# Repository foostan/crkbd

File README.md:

# Corne keyboard

The Corne keyboard is a split keyboard with 3x6 column staggered keys
and 3 thumb keys, based on [Helix](https://github.com/MakotoKurauchi/helix).
Crkbd stands for Corne Keyboard.

## Latest versions
- corne-cherry: for Cherry MX compatible switches

  - v4 Hotswappable ([JP](docs/corne-cherry/v4/buildguide_jp.md)/[EN](docs/corne-cherry/v4/buildguide_en.md))
  - v4 Soldering (will be released)
- corne-chocolate: for Kailh choc v1 and v2 switches
  - v4 Hotswappable ([JP](docs/corne-chocolate/v4/buildguide_jp.md)/[EN](docs/corne-chocolate/v4/buildguide_en.md)):
  - v4 Soldering (will be released)

## Old versions

- corne-classic: for Cherry MX compatible switches 
  - v1 Soldering: ([JP](docs/corne-classic/buildguide_jp.md)/[EN](docs/corne-classic/buildguide_en.md))
- corne-cherry: for Cherry MX compatible switches
  - v2 Hotswappable: ([JP](docs/corne-cherry/v2/buildguide_jp.md)/[EN](docs/corne-cherry/v2/buildguide_en.md))
  - v2 Hotswappable tilting version: ([tilting, JP](docs/corne-cherry/v2/buildguide_tilting_tenting_plate_jp.md)/[tilting, EN](docs/corne-cherry/v2/buildguide_tilting_tenting_plate_en.md)):
  - v3 Hotswappable: ([JP](docs/corne-cherry/v3/buildguide_jp.md)/[EN](docs/corne-cherry/v3/buildguide_en.md))
- corne-chocolate: for Kailh choc v1 switches
  - v2 Hotswappable: ([JP](docs/corne-chocolate/v2/buildguide_jp.md)/[EN](docs/corne-chocolate/v2/buildguide_en.md)):
- corne-light: for easy build with a simple PCB
  - v1 Soldering: ([JP](docs/corne-light/v1/buildguide_jp.md)/[EN](docs/corne-light/v1/buildguide_en.md)):
  - v2 Soldering: ([JP](docs/corne-light/v2/buildguide_low_edition_jp.md)/[EN](docs/corne-light/v2/buildguide_low_edition_en.md)):

## Notice
There are currently reports of a bug in v4.* caused by electromagnetic interference. Depending on the environment, one or both of the left and right keyboards may stop working. It is known that this is often caused by EMI emitted by mobile phones. If you experience this kind of problem, reconnect the USB, move the EMI-generating device (probably a mobile phone) more than 30 cm away from the keyboard, and observe the situation.

For more details, please see this issue. We look forward to receiving any new information.
https://github.com/foostan/crkbd/issues/265

## Images

### Cherry

### Chocolate

### Drawing

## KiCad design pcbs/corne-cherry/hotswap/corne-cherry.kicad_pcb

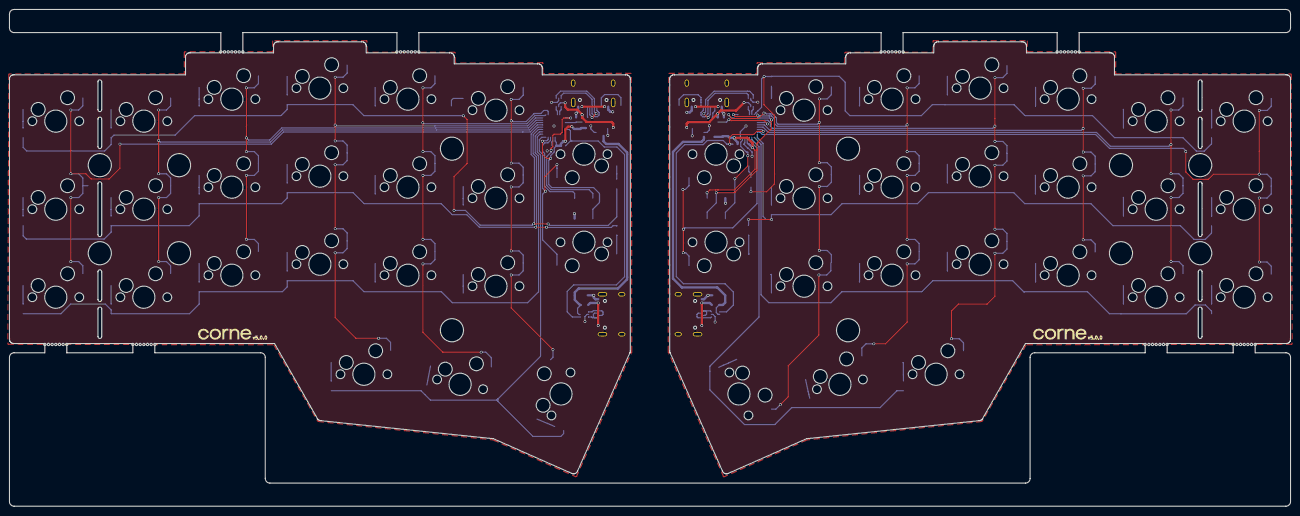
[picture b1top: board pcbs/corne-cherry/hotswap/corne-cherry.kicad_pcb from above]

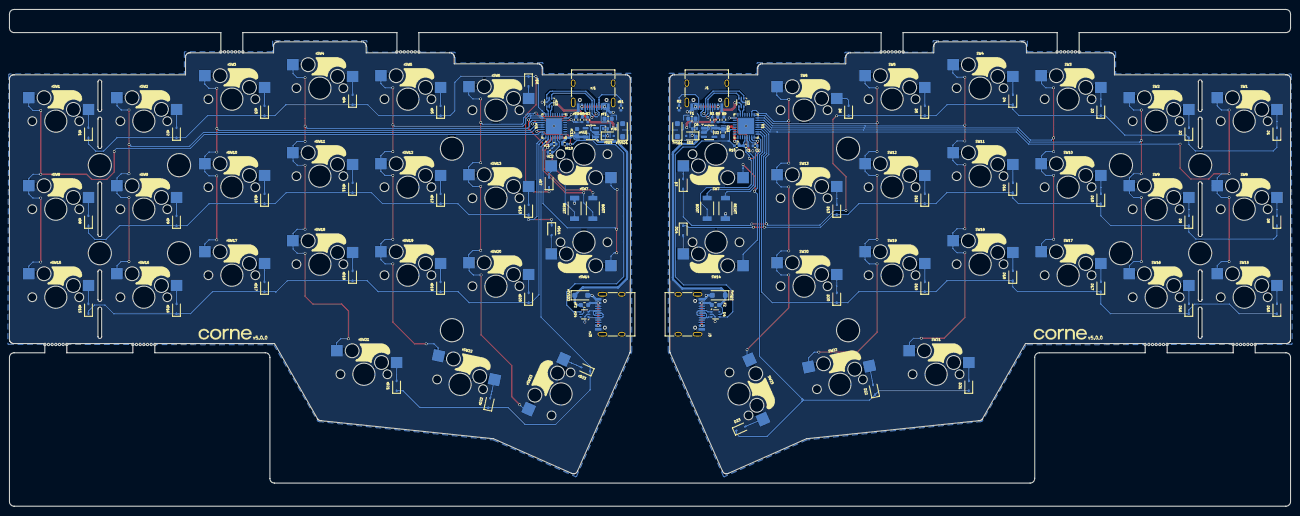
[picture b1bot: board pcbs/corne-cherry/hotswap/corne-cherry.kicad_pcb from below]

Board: 2 copper layers, 277.2 x 107.5 mm, 144 parts (136 on the bottom side), 104 nets.

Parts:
BOOT1: TS-1088-AR02016; TS-1088R-02026
BT1, BT2, BT3, BT4: Breakaway Tabs; Breakaway_Tabs
C1, C2: 100nF 16V X7R; C_0402_1005Metric
C6: 1uF 25V X5R; C_0402_1005Metric
C11: 4.7uF 16V X5R; C_0603_1608Metric
D1, D2, D3, D4, D5, D6, D7, D8, D9, D10, D11, D12, D13, D14, D15, D16, D17, D18, D19, D20, D21, D22, D23: 1N4148WS; D_SOD-323
F1, F2: 0603L025/24XR; Fuse_0603_1608Metric
J1, J3: TYPE-C-31-M-12; USB_C_Receptacle_HRO_TYPE-C-31-M-12
NRST1: TS-1088-AR02016; TS-1088R-02026
R1, R2: 5.1k; R_0402_1005Metric
R8: 5.6k; R_0402_1005Metric
R9: 10K; R_0402_1005Metric
R10: 4.7k; R_0402_1005Metric
SD1: PMEG4010CEJ,115; D_SOD-323F
SW1, SW2, SW3, SW4, SW5, SW6, SW7, SW8, SW9, SW10, SW11, SW12, SW13, SW14, SW15, SW16, SW17, SW18, SW19, SW20, SW21, SW22, SW23: CPG151101S11-16; keyswitch_mk_gateronlpv3_socket_1u
TVSD1, TVSD2: SMF5.0A; D_SOD-123F
U1: STM32G0B1KBU6; QFN-32-1EP_5x5mm_P0.5mm_EP3.45x3.45mm
U2: TPS70933DBVR; SOT-23-5
U3, U4: USBLC6-2P6; SOT-666
rBOOT1: TS-1088-AR02016; TS-1088R-02026
rBT1, rBT2, rBT3, rBT4: Breakaway Tabs; Breakaway_Tabs
rC1, rC2: 100nF 16V X7R; C_0402_1005Metric
rC6: 1uF 25V X5R; C_0402_1005Metric
rC11: 4.7uF 16V X5R; C_0603_1608Metric
rD1, rD2, rD3, rD4, rD5, rD6, rD7, rD8, rD9, rD10, rD11, rD12, rD13, rD14, rD15, rD16, rD17, rD18, rD19, rD20, rD21, rD22, rD23: 1N4148WS; D_SOD-323
rF1, rF2: 0603L025/24XR; Fuse_0603_1608Metric
rJ1, rJ3: TYPE-C-31-M-12; USB_C_Receptacle_HRO_TYPE-C-31-M-12
rNRST1: TS-1088-AR02016; TS-1088R-02026
rR1, rR2: 5.1k; R_0402_1005Metric
rR8: 5.6k; R_0402_1005Metric
rR9: 10K; R_0402_1005Metric
rR10: 4.7k; R_0402_1005Metric
rSD1: PMEG4010CEJ,115; D_SOD-323F
rSW1, rSW2, rSW3, rSW4, rSW5, rSW6, rSW7, rSW8, rSW9, rSW10, rSW11, rSW12, rSW13, rSW14, rSW15, rSW16, rSW17, rSW18, rSW19, rSW20, rSW21, rSW22, rSW23: CPG151101S11-16; keyswitch_mk_gateronlpv3_socket_1u
rTVSD1, rTVSD2: SMF5.0A; D_SOD-123F
rU1: STM32G0B1KBU6; QFN-32-1EP_5x5mm_P0.5mm_EP3.45x3.45mm
rU2: TPS70933DBVR; SOT-23-5
rU3, rU4: USBLC6-2P6; SOT-666

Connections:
/left/+3V3: BOOT1.2, C1.2, C11.1, R10.1, U1.4 (VDD), U1.7 (PA0), U2.5 (VOUT)
/left/+5V: C6.1, F2.2, SD1.1 (K), TVSD2.1 (K), U2.1 (VIN), U4.5 (VBUS)
/left/COL0: SW1.2, SW8.2, SW15.2, U1.13 (PA6)
/left/COL1: SW2.2, SW9.2, SW16.2, U1.14 (PA7)
/left/COL2: SW3.2, SW10.2, SW17.2, U1.15 (PB0)
/left/COL3: SW4.2, SW11.2, SW18.2, SW21.2, U1.16 (PB1)
/left/COL4: SW5.2, SW12.2, SW19.2, SW22.2, U1.17 (PB2)
/left/COL5: SW6.2, SW13.2, SW20.2, SW23.2, U1.18 (PA8)
/left/COL6: SW7.2, SW14.2, U1.8 (PA1)
/left/ROW0: D1.1 (K), D2.1 (K), D3.1 (K), D4.1 (K), D5.1 (K), D6.1 (K), D7.1 (K), U1.12 (PA5)
/left/ROW1: D8.1 (K), D9.1 (K), D10.1 (K), D11.1 (K), D12.1 (K), D13.1 (K), D14.1 (K), U1.11 (PA4)
/left/ROW2: D15.1 (K), D16.1 (K), D17.1 (K), D18.1 (K), D19.1 (K), D20.1 (K), U1.10 (PA3)
/left/ROW3: D21.1 (K), D22.1 (K), D23.1 (K), U1.9 (PA2)
/left/SERIAL: R10.2, U1.30 (PB6), U4.4 (I/O2)
/left/USB_DM: U1.22 (PA9/PA11), U3.6 (I/O1)
/left/USB_DP: U1.23 (PA10/PA12), U3.4 (I/O2)
/left/USB_VBUS_PIN: R8.2, R9.1, U1.27 (PB3)
/left/VBUS: F1.1, J1.A4 (VBUS), J1.A9 (VBUS), J1.B4 (VBUS), J1.B9 (VBUS)
/right/+3V3: rBOOT1.2, rC1.2, rC11.1, rR10.1, rU1.4 (VDD), rU2.5 (VOUT)
/right/+5V: rC6.1, rF2.2, rSD1.1 (K), rTVSD2.1 (K), rU2.1 (VIN), rU4.5 (VBUS)
/right/COL0: rSW1.2, rSW8.2, rSW15.2, rU1.31 (PB7)
/right/COL1: rSW2.2, rSW9.2, rSW16.2, rU1.29 (PB5)
/right/COL2: rSW3.2, rSW10.2, rSW17.2, rU1.28 (PB4)
/right/COL3: rSW4.2, rSW11.2, rSW18.2, rSW21.2, rU1.26 (PA15)
/right/COL4: rSW5.2, rSW12.2, rSW19.2, rSW22.2, rU1.17 (PB2)
/right/COL5: rSW6.2, rSW13.2, rSW20.2, rSW23.2, rU1.16 (PB1)
/right/COL6: rSW7.2, rSW14.2, rU1.3 (PC15)
/right/ROW0: rD1.1 (K), rD2.1 (K), rD3.1 (K), rD4.1 (K), rD5.1 (K), rD6.1 (K), rD7.1 (K), rU1.24 (PA13)
/right/ROW1: rD8.1 (K), rD9.1 (K), rD10.1 (K), rD11.1 (K), rD12.1 (K), rD13.1 (K), rD14.1 (K), rU1.32 (PB8)
/right/ROW2: rD15.1 (K), rD16.1 (K), rD17.1 (K), rD18.1 (K), rD19.1 (K), rD20.1 (K), rU1.1 (PB9)
/right/ROW3: rD21.1 (K), rD22.1 (K), rD23.1 (K), rU1.2 (PC14)
/right/SERIAL: rR10.2, rU1.30 (PB6), rU4.4 (I/O2)
/right/USB_DM: rU1.22 (PA9/PA11), rU3.6 (I/O1)
/right/USB_DP: rU1.23 (PA10/PA12), rU3.4 (I/O2)
/right/USB_VBUS_PIN: rR8.2, rR9.1, rU1.27 (PB3)
/right/VBUS: rF1.1, rJ1.A4 (VBUS), rJ1.A9 (VBUS), rJ1.B4 (VBUS), rJ1.B9 (VBUS)
GND: C1.1, C2.1, C6.2, C11.2, J1.A1 (GND), J1.A12 (GND), J1.B1 (GND), J1.B12 (GND), J1.SH (SHIELD), J3.A1 (GND), J3.A12 (GND), J3.B1 (GND), J3.B12 (GND), J3.SH (SHIELD), NRST1.1, R1.1, R2.1, R9.2, TVSD1.2 (A), TVSD2.2 (A), U1.5 (VSS), U1.33 (VSS), U2.2 (GND), U3.2 (GND), U4.2 (GND)
GNDR: rC1.1, rC2.1, rC6.2, rC11.2, rJ1.A1 (GND), rJ1.A12 (GND), rJ1.B1 (GND), rJ1.B12 (GND), rJ1.SH (SHIELD), rJ3.A1 (GND), rJ3.A12 (GND), rJ3.B1 (GND), rJ3.B12 (GND), rJ3.SH (SHIELD), rNRST1.1, rR1.1, rR2.1, rR9.2, rTVSD1.2 (A), rTVSD2.2 (A), rU1.5 (VSS), rU1.7 (PA0), rU1.33 (VSS), rU2.2 (GND), rU3.2 (GND), rU4.2 (GND)
unnamed: D1.2 (A), SW1.1
unnamed: D2.2 (A), SW2.1
unnamed: D3.2 (A), SW3.1
unnamed: D4.2 (A), SW4.1
unnamed: D5.2 (A), SW5.1
unnamed: D6.2 (A), SW6.1
unnamed: D7.2 (A), SW7.1
unnamed: D8.2 (A), SW8.1
unnamed: D9.2 (A), SW9.1
unnamed: D10.2 (A), SW10.1
unnamed: D11.2 (A), SW11.1
unnamed: D12.2 (A), SW12.1
unnamed: D13.2 (A), SW13.1
unnamed: D14.2 (A), SW14.1
unnamed: D15.2 (A), SW15.1
unnamed: D16.2 (A), SW16.1
unnamed: D17.2 (A), SW17.1
unnamed: D18.2 (A), SW18.1
unnamed: D19.2 (A), SW19.1
unnamed: D20.2 (A), SW20.1
unnamed: D21.2 (A), SW21.1
unnamed: D22.2 (A), SW22.1
unnamed: D23.2 (A), SW23.1
unnamed: F2.1, J3.A4 (VBUS), J3.A9 (VBUS), J3.B4 (VBUS), J3.B9 (VBUS)
unnamed: J1.A5 (CC1), R1.2
unnamed: J1.B5 (CC2), R2.2
unnamed: J1.A6 (D+), J1.B6 (D+), U3.3 (I/O2)
unnamed: J1.A7 (D-), J1.B7 (D-), U3.1 (I/O1)
unnamed: J3.A6 (D+), J3.B6 (D+), U4.3 (I/O2)
unnamed: J3.A7 (D-), J3.B7 (D-), U4.1 (I/O1)
unnamed: F1.2, R8.1, SD1.2 (A), TVSD1.1 (K), U3.5 (VBUS)
unnamed: BOOT1.1, U1.25 (PA14)
unnamed: C2.2, NRST1.2, U1.6 (PF2)
unnamed: rD1.2 (A), rSW1.1
unnamed: rD2.2 (A), rSW2.1
unnamed: rD3.2 (A), rSW3.1
unnamed: rD4.2 (A), rSW4.1
unnamed: rD5.2 (A), rSW5.1
unnamed: rD6.2 (A), rSW6.1
unnamed: rD7.2 (A), rSW7.1
unnamed: rD8.2 (A), rSW8.1
unnamed: rD9.2 (A), rSW9.1
unnamed: rD10.2 (A), rSW10.1
unnamed: rD11.2 (A), rSW11.1
unnamed: rD12.2 (A), rSW12.1
unnamed: rD13.2 (A), rSW13.1
unnamed: rD14.2 (A), rSW14.1
unnamed: rD15.2 (A), rSW15.1
unnamed: rD16.2 (A), rSW16.1
unnamed: rD17.2 (A), rSW17.1
unnamed: rD18.2 (A), rSW18.1
unnamed: rD19.2 (A), rSW19.1
unnamed: rD20.2 (A), rSW20.1
unnamed: rD21.2 (A), rSW21.1
unnamed: rD22.2 (A), rSW22.1
unnamed: rD23.2 (A), rSW23.1
unnamed: rF2.1, rJ3.A4 (VBUS), rJ3.A9 (VBUS), rJ3.B4 (VBUS), rJ3.B9 (VBUS)
unnamed: rJ1.A5 (CC1), rR1.2
unnamed: rJ1.B5 (CC2), rR2.2
unnamed: rJ1.A6 (D+), rJ1.B6 (D+), rU3.3 (I/O2)
unnamed: rJ1.A7 (D-), rJ1.B7 (D-), rU3.1 (I/O1)
unnamed: rJ3.A6 (D+), rJ3.B6 (D+), rU4.3 (I/O2)
unnamed: rJ3.A7 (D-), rJ3.B7 (D-), rU4.1 (I/O1)
unnamed: rF1.2, rR8.1, rSD1.2 (A), rTVSD1.1 (K), rU3.5 (VBUS)
unnamed: rBOOT1.1, rU1.25 (PA14)
unnamed: rC2.2, rNRST1.2, rU1.6 (PF2)

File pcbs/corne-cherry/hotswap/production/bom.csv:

Designator,Footprint,Quantity,Value,LCSC Part #
"BOOT1, NRST1, RBOOT1, RNRST1",TS-1088R-02026,4,TS-1088-AR02016,C720477
"BT1, BT2, BT3, BT4, RBT1, RBT2, RBT3, RBT4",Breakaway_Tabs,8,Breakaway Tabs,
"C1, C2, RC1, RC2",0402,4,100nF 16V X7R,C1525
"C11, RC11",0603,2,4.7uF 16V X5R,C19666
"C6, RC6",0402,2,1uF 25V X5R,C52923
"D1, D10, D11, D12, D13, D14, D15, D16, D17, D18, D19, D2, D20, D21, D22, D23, D3, D4, D5, D6, D7, D8, D9, RD1, RD10, RD11, RD12, RD13, RD14, RD15, RD16, RD17, RD18, RD19, RD2, RD20, RD21, RD22, RD23, RD3, RD4, RD5, RD6, RD7, RD8, RD9",D_SOD-323,46,1N4148WS,C727111
"F1, F2, RF1, RF2",0603,4,0603L025/24XR,C7472531
"J1, J3, RJ1, RJ3",USB_C_Receptacle_HRO_TYPE-C-31-M-12,4,TYPE-C-31-M-12,C165948
"R1, R2, RR1, RR2",0402,4,5.1k,C25905
"R10, RR10",0402,2,4.7k,C25900
"R8, RR8",0402,2,5.6k,C25908
"R9, RR9",0402,2,10K,C25744
"RSD1, SD1",D_SOD-323F,2,"PMEG4010CEJ,115",C50704
"RSW1, RSW10, RSW11, RSW12, RSW13, RSW14, RSW15, RSW16, RSW17, RSW18, RSW19, RSW2, RSW20, RSW21, RSW22, RSW23, RSW3, RSW4, RSW5, RSW6, RSW7, RSW8, RSW9, SW1, SW10, SW11, SW12, SW13, SW14, SW15, SW16, SW17, SW18, SW19, SW2, SW20, SW21, SW22, SW23, SW3, SW4, SW5, SW6, SW7, SW8, SW9",keyswitch_mk_gateronlpv3_socket_1u,46,CPG151101S11-16,C41430893
"RTVSD1, RTVSD2, TVSD1, TVSD2",D_SOD-123F,4,SMF5.0A,C151296
"RU1, U1",QFN-32-1EP_5x5mm_P0.5mm_EP3.45x3.45mm,2,STM32G0B1KBU6,C5159549
"RU2, U2",SOT-23-5,2,TPS70933DBVR,C89347
"RU3, RU4, U3, U4",SOT-666,4,USBLC6-2P6,C15999

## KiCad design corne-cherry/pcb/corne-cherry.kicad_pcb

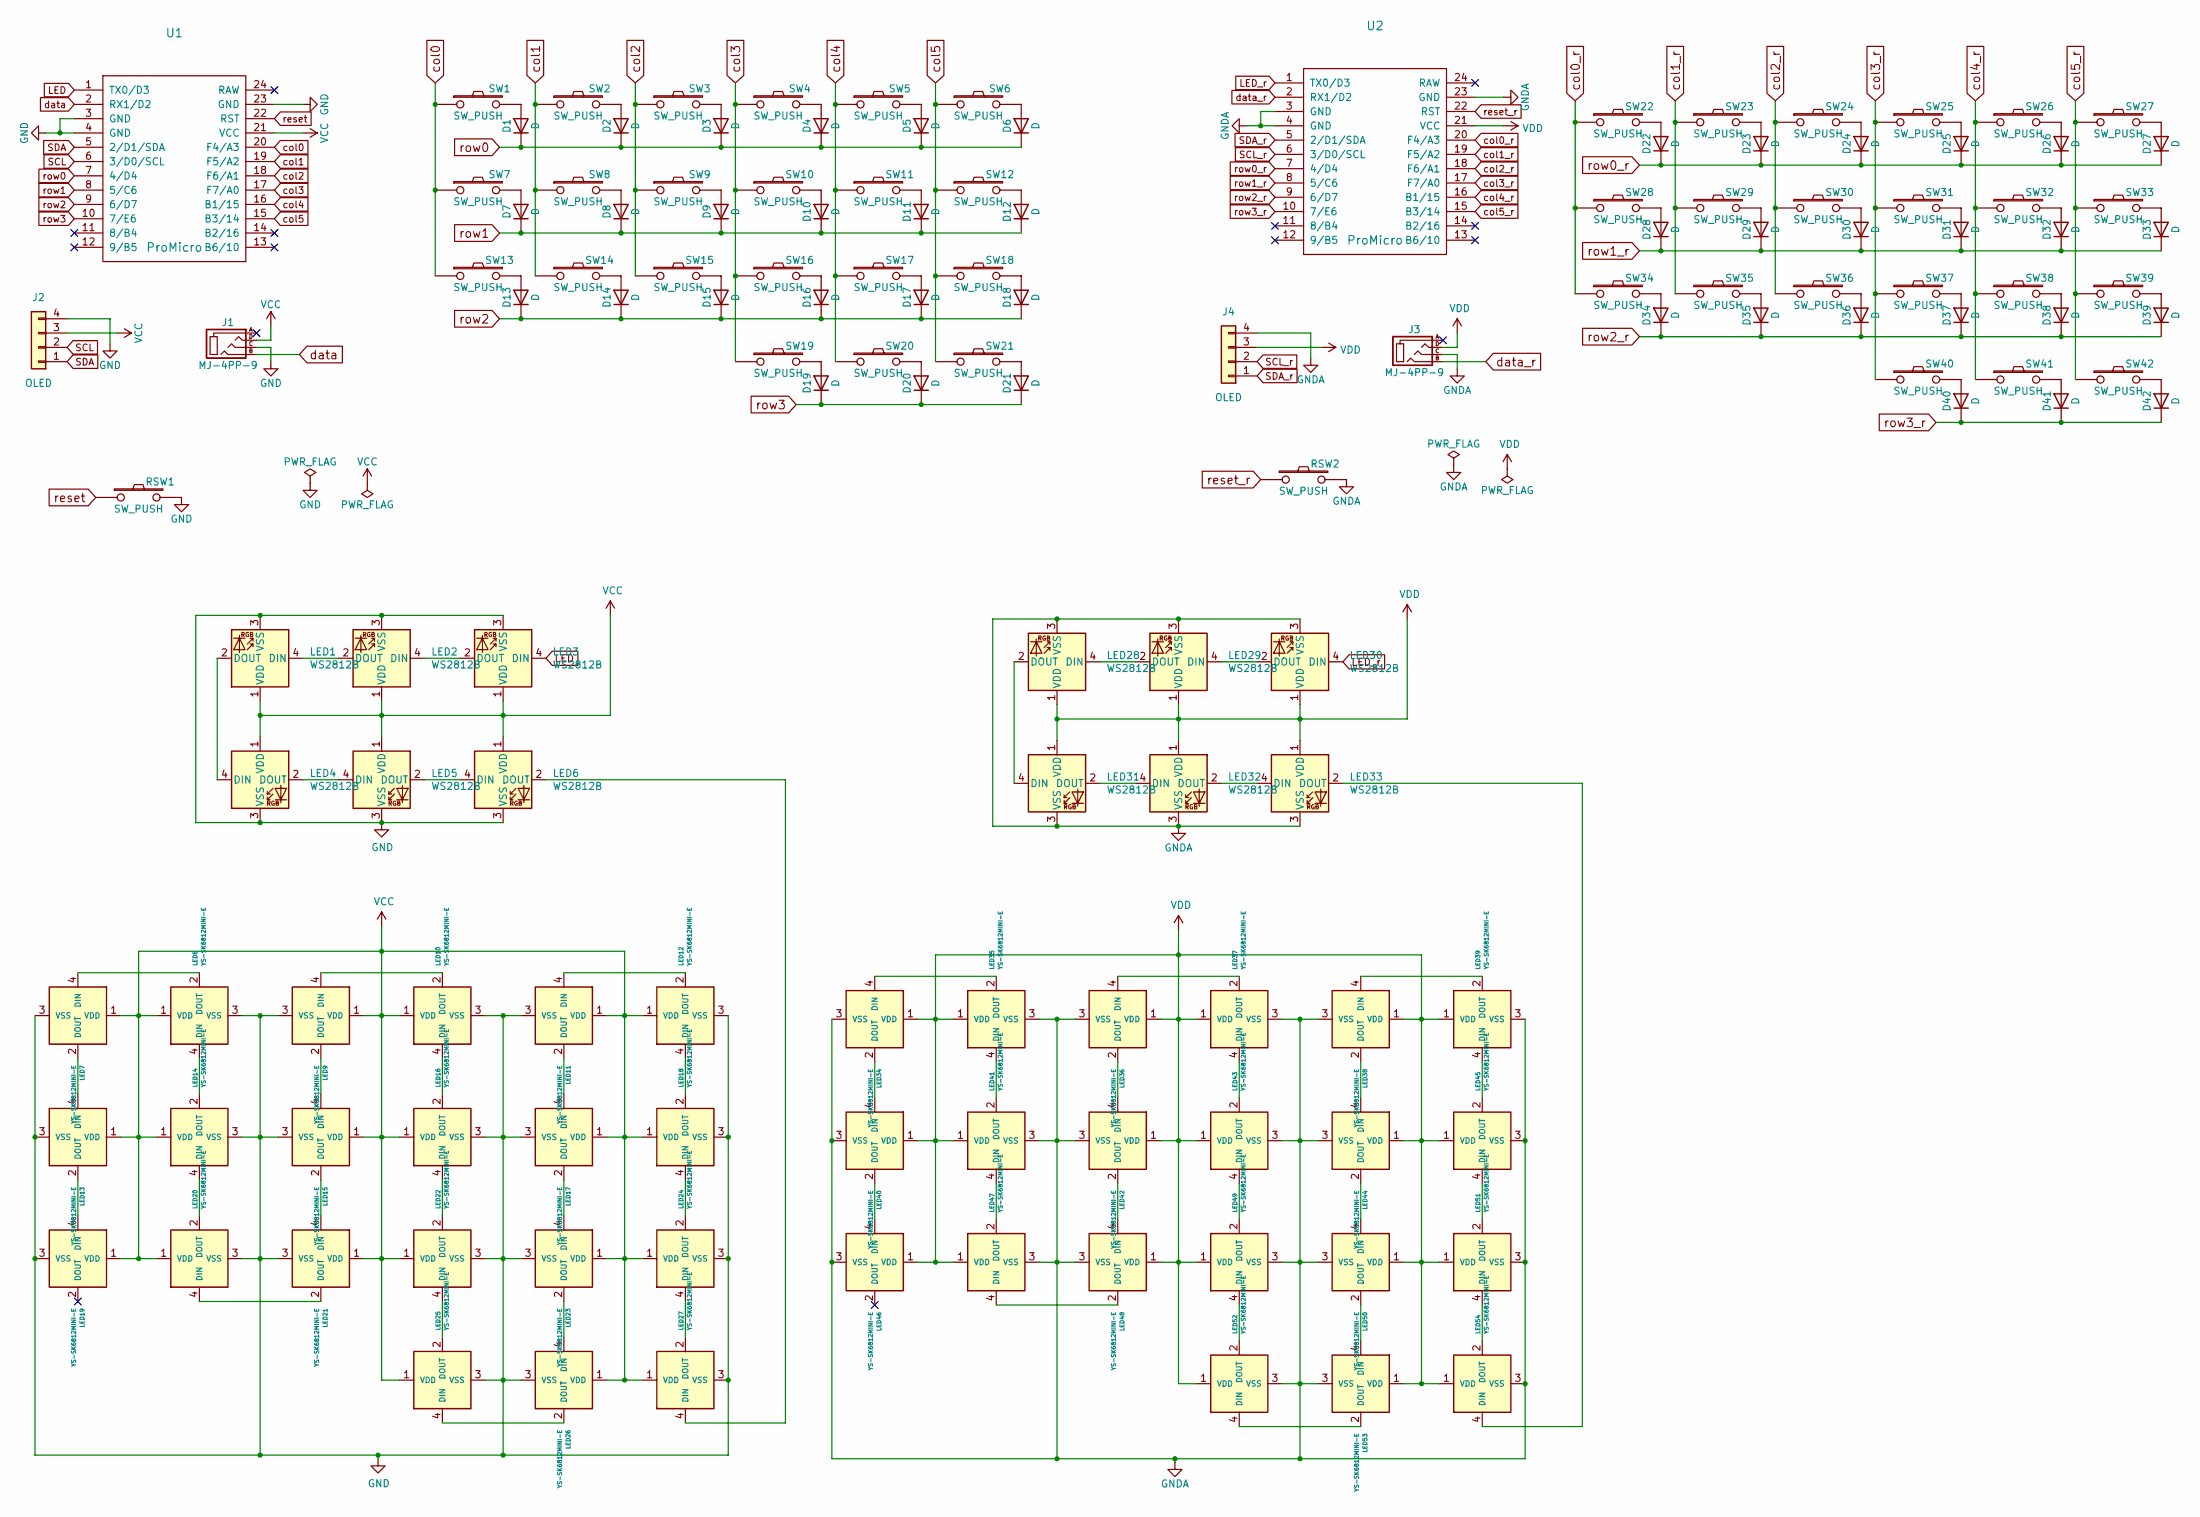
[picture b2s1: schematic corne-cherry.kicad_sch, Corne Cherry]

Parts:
D1, D2, D3, D4, D5, D6, D7, D8, D9, D10, D11, D12, D13, D14, D15, D16, D17, D18, D19, D20, D21, D22, D23, D24, D25, D26, D27, D28, D29, D30, D31, D32, D33, D34, D35, D36, D37, D38, D39, D40, D41, D42: D; D3_SMD_v2
J1, J3: MJ-4PP-9; MJ-4PP-9_1side
J2, J4: OLED; OLED_1side
LED1, LED2, LED3, LED4, LED5, LED6, LED28, LED29, LED30, LED31, LED32, LED33: WS2812B; LED_WS2812B_PLCC4_5.0x5.0mm_P3.2mm
LED7, LED8, LED9, LED10, LED11, LED12, LED13, LED14, LED15, LED16, LED17, LED18, LED19, LED20, LED21, LED22, LED23, LED24, LED25, LED26, LED27, LED34, LED35, LED36, LED37, LED38, LED39, LED40, LED41, LED42, LED43, LED44, LED45, LED46, LED47, LED48, LED49, LED50, LED51, LED52, LED53, LED54: YS-SK6812MINI-E
RSW1, RSW2: SW_PUSH; ResetSW_1side
SW1, SW2, SW3, SW4, SW5, SW6, SW7, SW8, SW9, SW10, SW11, SW12, SW13, SW14, SW15, SW16, SW17, SW18, SW19, SW20, SW22, SW23, SW24, SW25, SW26, SW27, SW28, SW29, SW30, SW31, SW32, SW33, SW34, SW35, SW36, SW37, SW38, SW39, SW40, SW41: SW_PUSH; CherryMX_Hotswap
SW21, SW42: SW_PUSH; CherryMX_Hotswap_1.5u
U1, U2: ProMicro; ProMicro_v3

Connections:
GND: J1.C, J2.4, LED1.3 (VSS), LED2.3 (VSS), LED3.3 (VSS), LED4.3 (VSS), LED5.3 (VSS), LED6.3 (VSS), LED7.3 (VSS), LED8.3 (VSS), LED9.3 (VSS), LED10.3 (VSS), LED11.3 (VSS), LED12.3 (VSS), LED13.3 (VSS), LED14.3 (VSS), LED15.3 (VSS), LED16.3 (VSS), LED17.3 (VSS), LED18.3 (VSS), LED19.3 (VSS), LED20.3 (VSS), LED21.3 (VSS), LED22.3 (VSS), LED23.3 (VSS), LED24.3 (VSS), LED25.3 (VSS), LED26.3 (VSS), LED27.3 (VSS), RSW1.2, U1.3 (GND), U1.4 (GND), U1.23 (GND)
GNDA: J3.C, J4.4, LED28.3 (VSS), LED29.3 (VSS), LED30.3 (VSS), LED31.3 (VSS), LED32.3 (VSS), LED33.3 (VSS), LED34.3 (VSS), LED35.3 (VSS), LED36.3 (VSS), LED37.3 (VSS), LED38.3 (VSS), LED39.3 (VSS), LED40.3 (VSS), LED41.3 (VSS), LED42.3 (VSS), LED43.3 (VSS), LED44.3 (VSS), LED45.3 (VSS), LED46.3 (VSS), LED47.3 (VSS), LED48.3 (VSS), LED49.3 (VSS), LED50.3 (VSS), LED51.3 (VSS), LED52.3 (VSS), LED53.3 (VSS), LED54.3 (VSS), RSW2.2, U2.3 (GND), U2.4 (GND), U2.23 (GND)
LED: LED3.4 (DIN), U1.1 (TX0/D3)
LED_r: LED30.4 (DIN), U2.1 (TX0/D3)
unnamed: D1.2 (A), SW1.2
unnamed: D2.2 (A), SW2.2
unnamed: D3.2 (A), SW3.2
unnamed: D4.2 (A), SW4.2
unnamed: D5.2 (A), SW5.2
unnamed: D6.2 (A), SW6.2
unnamed: D7.2 (A), SW7.2
unnamed: D8.2 (A), SW8.2
unnamed: D9.2 (A), SW9.2
unnamed: D10.2 (A), SW10.2
unnamed: D11.2 (A), SW11.2
unnamed: D12.2 (A), SW12.2
unnamed: D13.2 (A), SW13.2
unnamed: D14.2 (A), SW14.2
unnamed: D15.2 (A), SW15.2
unnamed: D16.2 (A), SW16.2
unnamed: D17.2 (A), SW17.2
unnamed: D18.2 (A), SW18.2
unnamed: D19.2 (A), SW19.2
unnamed: D20.2 (A), SW20.2
unnamed: D21.2 (A), SW21.2
unnamed: D22.2 (A), SW22.2
unnamed: D23.2 (A), SW23.2
unnamed: D24.2 (A), SW24.2
unnamed: D25.2 (A), SW25.2
unnamed: D26.2 (A), SW26.2
unnamed: D27.2 (A), SW27.2
unnamed: D28.2 (A), SW28.2
unnamed: D29.2 (A), SW29.2
unnamed: D30.2 (A), SW30.2
unnamed: D31.2 (A), SW31.2
unnamed: D32.2 (A), SW32.2
unnamed: D33.2 (A), SW33.2
unnamed: D34.2 (A), SW34.2
unnamed: D35.2 (A), SW35.2
unnamed: D36.2 (A), SW36.2
unnamed: D37.2 (A), SW37.2
unnamed: D38.2 (A), SW38.2
unnamed: D39.2 (A), SW39.2
unnamed: D40.2 (A), SW40.2
unnamed: D41.2 (A), SW41.2
unnamed: D42.2 (A), SW42.2
unnamed: LED1.2 (DOUT), LED4.4 (DIN)
unnamed: LED1.4 (DIN), LED2.2 (DOUT)
unnamed: LED2.4 (DIN), LED3.2 (DOUT)
unnamed: LED4.2 (DOUT), LED5.4 (DIN)
unnamed: LED5.2 (DOUT), LED6.4 (DIN)
unnamed: LED7.4 (DIN), LED8.2 (DOUT)
unnamed: LED9.4 (DIN), LED10.2 (DOUT)
unnamed: LED10.4 (DIN), LED16.2 (DOUT)
unnamed: LED11.2 (DOUT), LED17.4 (DIN)
unnamed: LED11.4 (DIN), LED12.2 (DOUT)
unnamed: LED12.4 (DIN), LED18.2 (DOUT)
unnamed: LED13.2 (DOUT), LED19.4 (DIN)
unnamed: LED7.2 (DOUT), LED13.4 (DIN)
unnamed: LED8.4 (DIN), LED14.2 (DOUT)
unnamed: LED14.4 (DIN), LED20.2 (DOUT)
unnamed: LED15.2 (DOUT), LED21.4 (DIN)
unnamed: LED9.2 (DOUT), LED15.4 (DIN)
unnamed: LED16.4 (DIN), LED22.2 (DOUT)
unnamed: LED17.2 (DOUT), LED23.4 (DIN)
unnamed: LED18.4 (DIN), LED24.2 (DOUT)
unnamed: LED20.4 (DIN), LED21.2 (DOUT)
unnamed: LED22.4 (DIN), LED25.2 (DOUT)
unnamed: LED23.2 (DOUT), LED26.4 (DIN)
unnamed: LED24.4 (DIN), LED27.2 (DOUT)
unnamed: LED25.4 (DIN), LED26.2 (DOUT)
unnamed: LED6.2 (DOUT), LED27.4 (DIN)
unnamed: LED28.2 (DOUT), LED31.4 (DIN)
unnamed: LED28.4 (DIN), LED29.2 (DOUT)
unnamed: LED29.4 (DIN), LED30.2 (DOUT)
unnamed: LED31.2 (DOUT), LED32.4 (DIN)
unnamed: LED32.2 (DOUT), LED33.4 (DIN)
unnamed: LED33.2 (DOUT), LED54.4 (DIN)
unnamed: LED34.2 (DOUT), LED40.4 (DIN)
unnamed: LED34.4 (DIN), LED35.2 (DOUT)
unnamed: LED35.4 (DIN), LED41.2 (DOUT)
unnamed: LED36.2 (DOUT), LED42.4 (DIN)
unnamed: LED36.4 (DIN), LED37.2 (DOUT)
unnamed: LED37.4 (DIN), LED43.2 (DOUT)
unnamed: LED38.2 (DOUT), LED44.4 (DIN)
unnamed: LED38.4 (DIN), LED39.2 (DOUT)
unnamed: LED39.4 (DIN), LED45.2 (DOUT)
unnamed: LED40.2 (DOUT), LED46.4 (DIN)
unnamed: LED41.4 (DIN), LED47.2 (DOUT)
unnamed: LED42.2 (DOUT), LED48.4 (DIN)
unnamed: LED43.4 (DIN), LED49.2 (DOUT)
unnamed: LED44.2 (DOUT), LED50.4 (DIN)
unnamed: LED45.4 (DIN), LED51.2 (DOUT)
unnamed: LED47.4 (DIN), LED48.2 (DOUT)
unnamed: LED49.4 (DIN), LED52.2 (DOUT)
unnamed: LED50.2 (DOUT), LED53.4 (DIN)
unnamed: LED51.4 (DIN), LED54.2 (DOUT)
unnamed: LED52.4 (DIN), LED53.2 (DOUT)
SCL: J2.2, U1.6 (3/D0/SCL)
SCL_r: J4.2, U2.6 (3/D0/SCL)
SDA: J2.1, U1.5 (2/D1/SDA)
SDA_r: J4.1, U2.5 (2/D1/SDA)
VCC: J1.D, J2.3, LED1.1 (VDD), LED2.1 (VDD), LED3.1 (VDD), LED4.1 (VDD), LED5.1 (VDD), LED6.1 (VDD), LED7.1 (VDD), LED8.1 (VDD), LED9.1 (VDD), LED10.1 (VDD), LED11.1 (VDD), LED12.1 (VDD), LED13.1 (VDD), LED14.1 (VDD), LED15.1 (VDD), LED16.1 (VDD), LED17.1 (VDD), LED18.1 (VDD), LED19.1 (VDD), LED20.1 (VDD), LED21.1 (VDD), LED22.1 (VDD), LED23.1 (VDD), LED24.1 (VDD), LED25.1 (VDD), LED26.1 (VDD), LED27.1 (VDD), U1.21 (VCC)
VDD: J3.D, J4.3, LED28.1 (VDD), LED29.1 (VDD), LED30.1 (VDD), LED31.1 (VDD), LED32.1 (VDD), LED33.1 (VDD), LED34.1 (VDD), LED35.1 (VDD), LED36.1 (VDD), LED37.1 (VDD), LED38.1 (VDD), LED39.1 (VDD), LED40.1 (VDD), LED41.1 (VDD), LED42.1 (VDD), LED43.1 (VDD), LED44.1 (VDD), LED45.1 (VDD), LED46.1 (VDD), LED47.1 (VDD), LED48.1 (VDD), LED49.1 (VDD), LED50.1 (VDD), LED51.1 (VDD), LED52.1 (VDD), LED53.1 (VDD), LED54.1 (VDD), U2.21 (VCC)
col0: SW1.1, SW7.1, SW13.1, U1.20 (F4/A3)
col0_r: SW22.1, SW28.1, SW34.1, U2.20 (F4/A3)
col1: SW2.1, SW8.1, SW14.1, U1.19 (F5/A2)
col1_r: SW23.1, SW29.1, SW35.1, U2.19 (F5/A2)
col2: SW3.1, SW9.1, SW15.1, U1.18 (F6/A1)
col2_r: SW24.1, SW30.1, SW36.1, U2.18 (F6/A1)
col3: SW4.1, SW10.1, SW16.1, SW19.1, U1.17 (F7/A0)
col3_r: SW25.1, SW31.1, SW37.1, SW40.1, U2.17 (F7/A0)
col4: SW5.1, SW11.1, SW17.1, SW20.1, U1.16 (B1/15)
col4_r: SW26.1, SW32.1, SW38.1, SW41.1, U2.16 (B1/15)
col5: SW6.1, SW12.1, SW18.1, SW21.1, U1.15 (B3/14)
col5_r: SW27.1, SW33.1, SW39.1, SW42.1, U2.15 (B3/14)
data: J1.B, U1.2 (RX1/D2)
data_r: J3.B, U2.2 (RX1/D2)
reset: RSW1.1, U1.22 (RST)
reset_r: RSW2.1, U2.22 (RST)
row0: D1.1 (K), D2.1 (K), D3.1 (K), D4.1 (K), D5.1 (K), D6.1 (K), U1.7 (4/D4)
row0_r: D22.1 (K), D23.1 (K), D24.1 (K), D25.1 (K), D26.1 (K), D27.1 (K), U2.7 (4/D4)
row1: D7.1 (K), D8.1 (K), D9.1 (K), D10.1 (K), D11.1 (K), D12.1 (K), U1.8 (5/C6)
row1_r: D28.1 (K), D29.1 (K), D30.1 (K), D31.1 (K), D32.1 (K), D33.1 (K), U2.8 (5/C6)
row2: D13.1 (K), D14.1 (K), D15.1 (K), D16.1 (K), D17.1 (K), D18.1 (K), U1.9 (6/D7)
row2_r: D34.1 (K), D35.1 (K), D36.1 (K), D37.1 (K), D38.1 (K), D39.1 (K), U2.9 (6/D7)
row3: D19.1 (K), D20.1 (K), D21.1 (K), U1.10 (7/E6)
row3_r: D40.1 (K), D41.1 (K), D42.1 (K), U2.10 (7/E6)

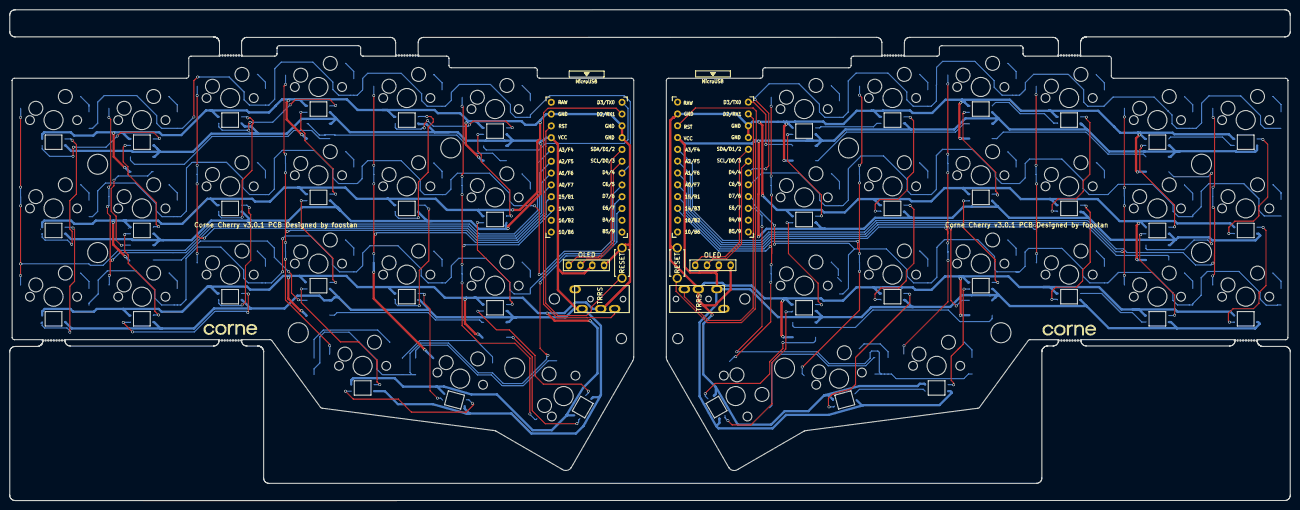
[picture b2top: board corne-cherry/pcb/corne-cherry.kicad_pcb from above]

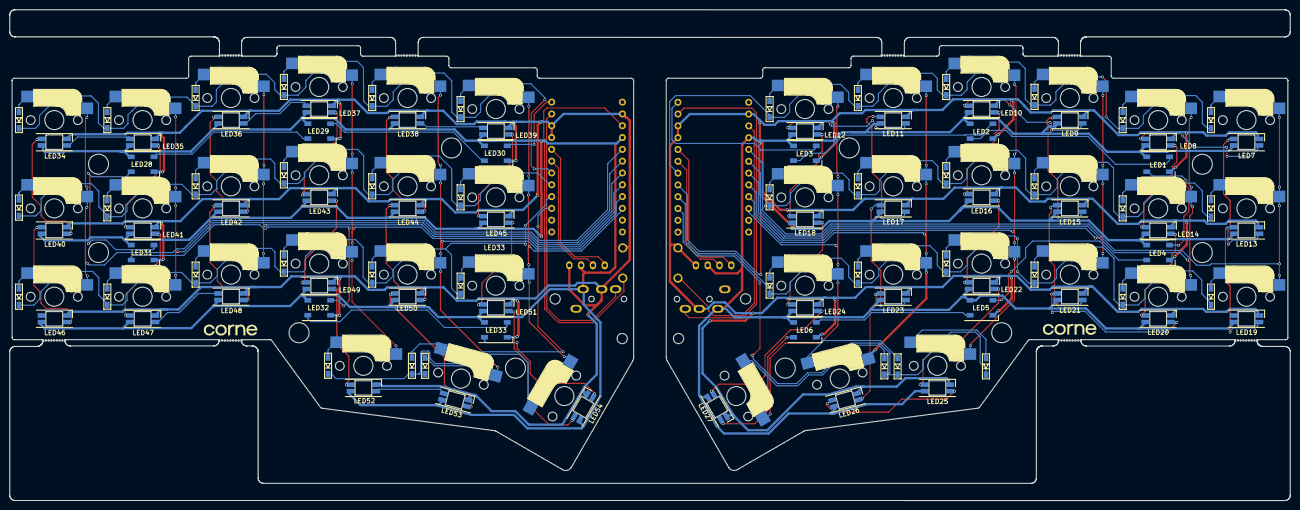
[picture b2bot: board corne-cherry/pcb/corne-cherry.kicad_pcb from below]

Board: 2 copper layers, 275.5 x 105.6 mm, 160 parts (99 on the bottom side), 128 nets.

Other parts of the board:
Ref**: Val**; M2_HOLE_v2
Ref**#2, Ref**#3, Ref**#4, Ref**#5, Ref**#6, Ref**#7, Ref**#8, Ref**#9, Ref**#10, Ref**#11, Ref**#12, Ref**#13, Ref**#14: Val**; M2_HOLE_v2
